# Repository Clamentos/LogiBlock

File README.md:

# Logi-Block

A simple, small, FPGA inspired, breadboardable logic cell implemented with discrete SMD components. It is composed of a fracturable 4-input LUT and a D-type flip-flop. It can perform any 4-to-1 or 4-to-2 boolean function and it can optionally store the result in its flip-flop. Logi-Block is programmable serially and can be combined with others to implement any logic circuit.

*Board revision 2*

### Manufacturing

Production files are provided in the releases section. For JLCPCB, the following files can be used:

- ```Logi-Block_2.zip```: ZIP containing the gerber files.
- ```bom.csv```: The bill of materials CSV file.
- ```positions.csv```: The component placement position CSV file.

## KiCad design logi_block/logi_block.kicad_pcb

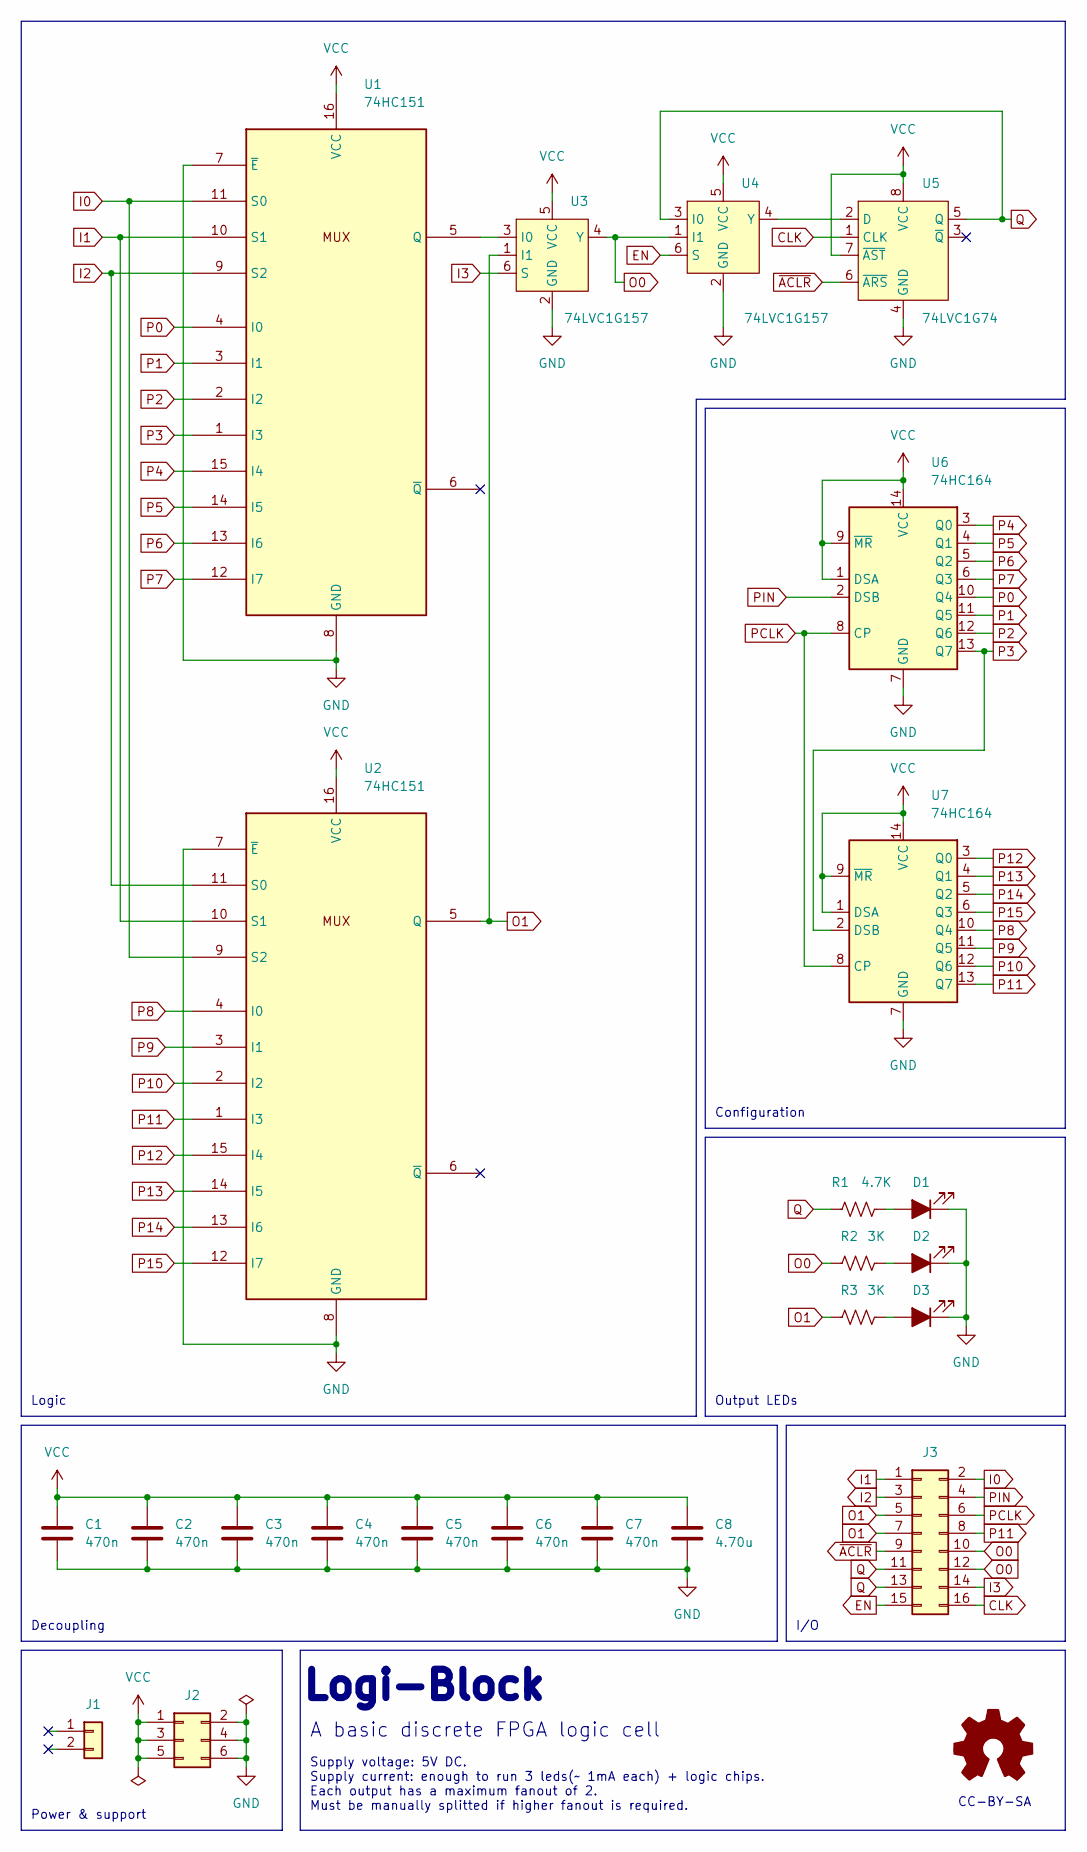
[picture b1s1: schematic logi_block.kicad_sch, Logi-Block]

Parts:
C1, C2, C3, C4, C5, C6, C7: 470n; C_0603_1608Metric; JLCPCB Part # C1623
C8: 4.70u; C_1206_3216Metric; JLCPCB Part # C29823
D1: LED_Filled; LED_0603_1608Metric; JLCPCB Part # C84267
D2: LED_Filled; LED_0603_1608Metric; JLCPCB Part # C84263
D3: LED_Filled; LED_0603_1608Metric; JLCPCB Part # C84266
J1: Conn_01x02; PinHeader_1x02_P2.54mm_Vertical_SMD_Pin1Left; JLCPCB Part # C5160785
J2: Conn_02x03_Odd_Even; PinHeader_2x03_P2.54mm_Vertical_SMD; JLCPCB Part # C3294461
J3: Conn_02x08_Odd_Even; PinHeader_2x08_P2.54mm_Vertical_SMD; JLCPCB Part # C32713288
R1: 4.7K; R_0603_1608Metric; JLCPCB Part # C23162
R2, R3: 3K; R_0603_1608Metric; JLCPCB Part # C4211
U1, U2: 74HC151; TSSOP-16_4.4x5mm_P0.65mm; JLCPCB Part # C152523
U3, U4: 74LVC1G157; SOT-363_SC-70-6; JLCPCB Part # C135822
U5: 74LVC1G74; XSON-8_L2.0-W1.0-P0.50-BL-A; JLCPCB Part # C548415
U6, U7: 74HC164; TSSOP-14_4.4x5mm_P0.65mm; JLCPCB Part # C406867

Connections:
CLK: J3.16, U5.1 (CLK)
EN: J3.15, U4.6 (S)
GND: C1.2, C2.2, C3.2, C4.2, C5.2, C6.2, C7.2, C8.2, D1.1 (K), D2.1 (K), D3.1 (K), J2.2, J2.4, J2.6, U1.7 (~E), U1.8 (GND), U2.7 (~E), U2.8 (GND), U3.2 (GND), U4.2 (GND), U5.4 (GND), U6.7 (GND), U7.7 (GND)
I0: J3.2, U1.11 (S0), U2.9 (S2)
I1: J3.1, U1.10 (S1), U2.10 (S1)
I2: J3.3, U1.9 (S2), U2.11 (S0)
I3: J3.14, U3.6 (S)
unnamed: D1.2 (A), R1.2
unnamed: D2.2 (A), R2.2
unnamed: D3.2 (A), R3.2
unnamed: U1.5 (Q), U3.3 (I0)
unnamed: U4.4 (Y), U5.2 (D)
O0: J3.10, J3.12, R2.1, U3.4 (Y), U4.1 (I1)
O1: J3.5, J3.7, R3.1, U2.5 (Q), U3.1 (I1)
P0: U1.4 (I0), U6.10 (Q4)
P1: U1.3 (I1), U6.11 (Q5)
P2: U1.2 (I2), U6.12 (Q6)
P3: U1.1 (I3), U6.13 (Q7), U7.2 (DSB)
P4: U1.15 (I4), U6.3 (Q0)
P5: U1.14 (I5), U6.4 (Q1)
P6: U1.13 (I6), U6.5 (Q2)
P7: U1.12 (I7), U6.6 (Q3)
P8: U2.4 (I0), U7.10 (Q4)
P9: U2.3 (I1), U7.11 (Q5)
P10: U2.2 (I2), U7.12 (Q6)
P11: J3.8, U2.1 (I3), U7.13 (Q7)
P12: U2.15 (I4), U7.3 (Q0)
P13: U2.14 (I5), U7.4 (Q1)
P14: U2.13 (I6), U7.5 (Q2)
P15: U2.12 (I7), U7.6 (Q3)
PCLK: J3.6, U6.8 (CP), U7.8 (CP)
PIN: J3.4, U6.2 (DSB)
Q: J3.11, J3.13, R1.1, U4.3 (I0), U5.5 (Q)
VCC: C1.1, C2.1, C3.1, C4.1, C5.1, C6.1, C7.1, C8.1, J2.1, J2.3, J2.5, U1.16 (VCC), U2.16 (VCC), U3.5 (VCC), U4.5 (VCC), U5.7 (~AST), U5.8 (VCC), U6.1 (DSA), U6.9 (~MR), U6.14 (VCC), U7.1 (DSA), U7.9 (~MR), U7.14 (VCC)
~ACLR: J3.9, U5.6 (~ARS)

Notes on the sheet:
A basic discrete FPGA logic cell
Supply voltage: 5V DC. Supply current: enough to run 3 leds(~ 1mA each) + logic chips. Each output has a maximum fanout of 2. Must be manually splitted if higher fanout is required.
CC-BY-SA
Decoupling
I/O
Power & support
Logic
Configuration
Output LEDs
Logi-Block

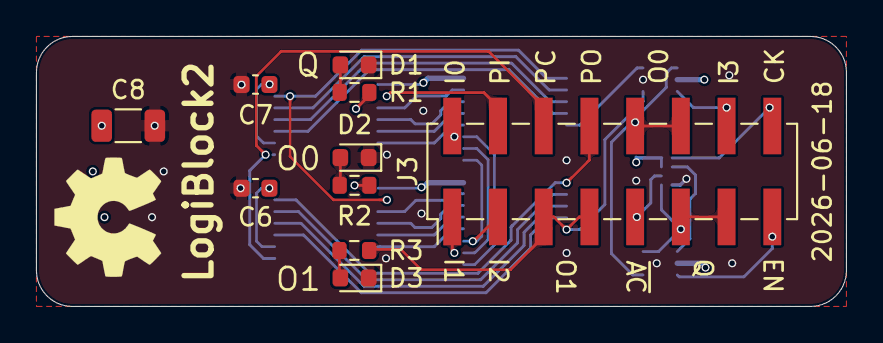
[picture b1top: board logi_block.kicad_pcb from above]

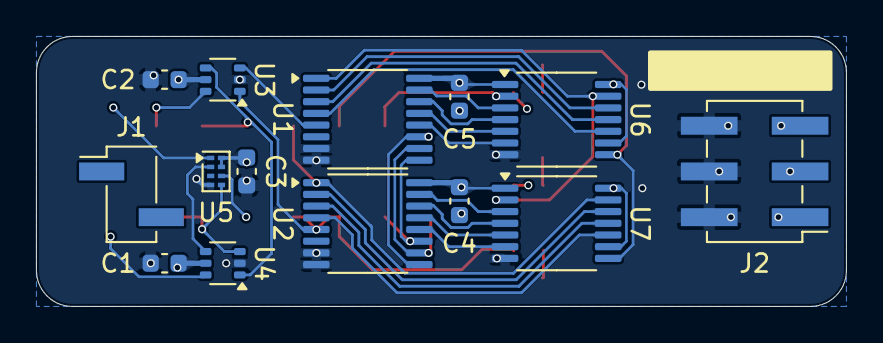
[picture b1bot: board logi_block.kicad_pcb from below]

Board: 6 copper layers, 45.0 x 15.0 mm, 24 parts (14 on the bottom side), 35 nets.

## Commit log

2025-10-18 Repo init.
2025-10-18 Added basic documentation.
2026-06-18 Maintenance on schematic Maintenance on PCB (changed serial number for JLCPCB) Added local datasheets Remade pictures Other small refactors...
2026-06-18 renamed files for better consistency
2026-06-18 committed the delete part of the renaming
